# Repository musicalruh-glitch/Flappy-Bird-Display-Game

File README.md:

### **Flappy Bird Display Game**

I built a hand held game, the in game name being  "Flappy Bird Soul." The game is inspired by Undertale, (like all my other Half Life projects) and it was originally supposed to be a Flappy Bird game, hence the name but it's inspired by the attack patterns in game Undertale, sharing the same sprites and music. All credits for sprites, attack patterns, style, and music go to Toby Fox, this product is not for commercial use, it's for my own leisure, because if they won't make the merch just make it yourself! In any case, go play Undertale, it's awesome :D

!!DISCLAIMER FOR THE READ ME!! If you are an Undertale fan, you will have a field day. If you are not, you will be bombarded by references.

---

---

### **How it works:**

As I've mentioned, the game itself is heavily inspired by Undertale, every bit of it. I've had to make modifications since they're not the same thing -- obviously, but think of it as Undertale if it was a handheld Flappy-ish Bird game.

When you press the on/off button on the side, you're greeted with the title "Flappy Bird Soul" on the menu, along with a saved High Score and the prompt PRESS ANY TO START. To get started here, press any of the 4 directional buttons on the device to trigger the startup chime and launch straight into battle.

On the active gameplay screen you'll see the Undertale rectangular Battle Box, the HP: 20/20 counter in the top left, and your live SCR (score) counter in the top right. The entity you control? It's the classic soul from Undertale! It moves smoothly in 4 directions w/ no gravity (so not exactly flappy bird haha...). You'll have to dodge incoming obstacles like Papyrus's bone pillars or Toriel's fireballs, -- the two added attack patterns! Every obstacle you successfully dodge increases your score. If an obstacle hits your soul, it plays a damage sound effect and reduces your HP by 1. Once your HP is 0 you lose :(((

And the classic Game Over screen! You'll see big bold text reading "GAME OVER" accompanied by a descending chiptune shard-break sound effect, followed by a PRESS ANY TO RESET. Classic reset. When you reach this screen, as instructed press any button to save your high score and return to the main intro menu.

Usually for games like Flappy Bird there is no way to win the game (as far as I know); but that felt a bit half-baked for my taste, so if you last against the battle attacks for 10 whopping minutes,  you get the YOU WIN! display screen and the device tracks your total wins. Once you reach here, press any button to return to the menu for another run.

---

---

### **!!IMPORTANT FOR BILL OF MATERIALS!!
In Halflife I was told to add all the materials I would be using including anything I already own at $0, but Halflife requires everything added to be a minimum of $0.01 so everything listed to be $0.01 are things I already have!! Look at the BOM below for instructions for the custom PCB, the rest is basically a repeat of what's written in the Halflife BOM. FOR THE CUSTOM PCB PLEASE CHANGE SHIPPING TO GLOBAL STANDARD DIRECT LINE AND CHANGE THE SURFACE FINISH FROM Hasl (with lead) TO LeadFree HASL.**

---

### **Flappy Bird Display Game Project Bill of Materials (BOM)**

| Part / Description | Qty | Unit Price | Total Price | Vendor | Link |
| --- | --- | --- | --- | --- | --- |
| **Custom PCB** (Fabricated circuit board) | 1 | $5.20 | $5.20 | JLCPCB | https://cart.jlcpcb.com/quote?stencilLayer=2&stencilWidth=100&stencilLength=100&stencilCounts=5&plateType=1&spm=Jlcpcb.Homepage.1010
| **Seed Studio XIAO ESP32-S3** (Microcontroller) | 1 | $1.51 | $1.51 | AliExpress | https://www.aliexpress.us/item/3256813209030802.html?src=google&src=google&albch=shopping&acnt=708-803-3821&isdl=y&slnk=&plac=&mtctp=&albbt=Google_7_shopping&aff_platform=google&aff_short_key=UneMJZVf&gclsrc=aw.ds&albagn=888888&ds_e_adid=&ds_e_matchtype=&ds_e_device=c&ds_e_network=x&ds_e_product_group_id=&ds_e_product_id=en3256813209030802&ds_e_product_merchant_id=5851713403&ds_e_product_country=US&ds_e_product_language=en&ds_e_product_channel=online&ds_e_product_store_id=&ds_url_v=2&albcp=19558607238&albag=&isSmbAutoCall=false&needSmbHouyi=false&gad_source=1&gad_campaignid=19566915268&gbraid=0AAAAAD6I-hEBTz-5jNlmDqvFRvfd-Af1r&gclid=CjwKCAjwgJHXBhBGEiwAHohJq0jmxRYXkAyNDjMiczX3DgCREABbyFcu1fEiNRO9FfYQuq9aGSnCexoC5ZEQAvD_BwE&gatewayAdapt=glo2usa
| **0.96 inch SPI OLED Display** (128x64 resolution) | 1 | $1.09 | $1.09 | AliExpress | https://www.aliexpress.us/item/3256810259894244.html?src=google&src=google&albch=shopping&acnt=708-803-3821&isdl=y&slnk=&plac=&mtctp=&albbt=Google_7_shopping&aff_platform=google&aff_short_key=UneMJZVf&gclsrc=aw.ds&albagn=888888&ds_e_adid=&ds_e_matchtype=&ds_e_device=c&ds_e_network=x&ds_e_product_group_id=&ds_e_product_id=en3256810259894244&ds_e_product_merchant_id=5851713403&ds_e_product_country=US&ds_e_product_language=en&ds_e_product_channel=online&ds_e_product_store_id=&ds_url_v=2&albcp=19558607238&albag=&isSmbAutoCall=false&needSmbHouyi=false&gad_source=1&gad_campaignid=19566915268&gbraid=0AAAAAD6I-hEBTz-5jNlmDqvFRvfd-Af1r&gclid=CjwKCAjwgJHXBhBGEiwAHohJqw27ODRaYlOE_lPz4eLpTx0uXy4irya2ANM2uJhlEW0BOKlUSSg7PhoCdeUQAvD_BwE&gatewayAdapt=glo2usa
| **Tactile Push Buttons** | 1 | $1.09 | $1.09 | AliExpress | https://www.aliexpress.us/item/3256808376799054.html?src=google&src=google&albch=shopping&acnt=708-803-3821&isdl=y&slnk=&plac=&mtctp=&albbt=Google_7_shopping&aff_platform=google&aff_short_key=UneMJZVf&gclsrc=aw.ds&albagn=888888&ds_e_adid=&ds_e_matchtype=&ds_e_device=c&ds_e_network=x&ds_e_product_group_id=&ds_e_product_id=en3256808376799054&ds_e_product_merchant_id=5851713403&ds_e_product_country=US&ds_e_product_language=en&ds_e_product_channel=online&ds_e_product_store_id=&ds_url_v=2&albcp=19558607238&albag=&isSmbAutoCall=false&needSmbHouyi=false&gad_source=4&gad_campaignid=19566915268&gbraid=0AAAAAD6I-hGDbaypQSEg9FIsHYtTg3l-U&gclid=CjwKCAjwgJHXBhBGEiwAHohJq2HiYEh7Nx0f8b8VAlV9QLfA9kqLMiwbQNcA2PXyUyvbKBT3iwDi2RoCYD0QAvD_BwE&gatewayAdapt=glo2usa
| **Piezo Buzzer** | 1 | $1.09 | $1.09 | AliExpress | https://www.aliexpress.us/item/3256806026983317.html?src=google&src=google&albch=shopping&acnt=708-803-3821&isdl=y&slnk=&plac=&mtctp=&albbt=Google_7_shopping&aff_platform=google&aff_short_key=UneMJZVf&gclsrc=aw.ds&albagn=888888&ds_e_adid=&ds_e_matchtype=&ds_e_device=c&ds_e_network=x&ds_e_product_group_id=&ds_e_product_id=en3256806026983317&ds_e_product_merchant_id=5851713403&ds_e_product_country=US&ds_e_product_language=en&ds_e_product_channel=online&ds_e_product_store_id=&ds_url_v=2&albcp=19558607238&albag=&isSmbAutoCall=false&needSmbHouyi=false&gad_source=1&gad_campaignid=19566915268&gbraid=0AAAAAD6I-hEBTz-5jNlmDqvFRvfd-Af1r&gclid=CjwKCAjwgJHXBhBGEiwAHohJq_DGYuMpHG2ntfV_2_tf42pQ_JDr3ubO-9eQ19pHfD63iBxA8MtnLxoCD8EQAvD_BwE&gatewayAdapt=glo2usa

*Use gerber files to drag and drop in JLCPCB to order, and change shipping to Global Standard Direct Line
*Total Tax calculated is based off the fact that items that share the same source are put into a cart and then the shipping tax used for those items is combined to minimize cost
* **Total Tax & Shipping for the whole order:** $4.99

---

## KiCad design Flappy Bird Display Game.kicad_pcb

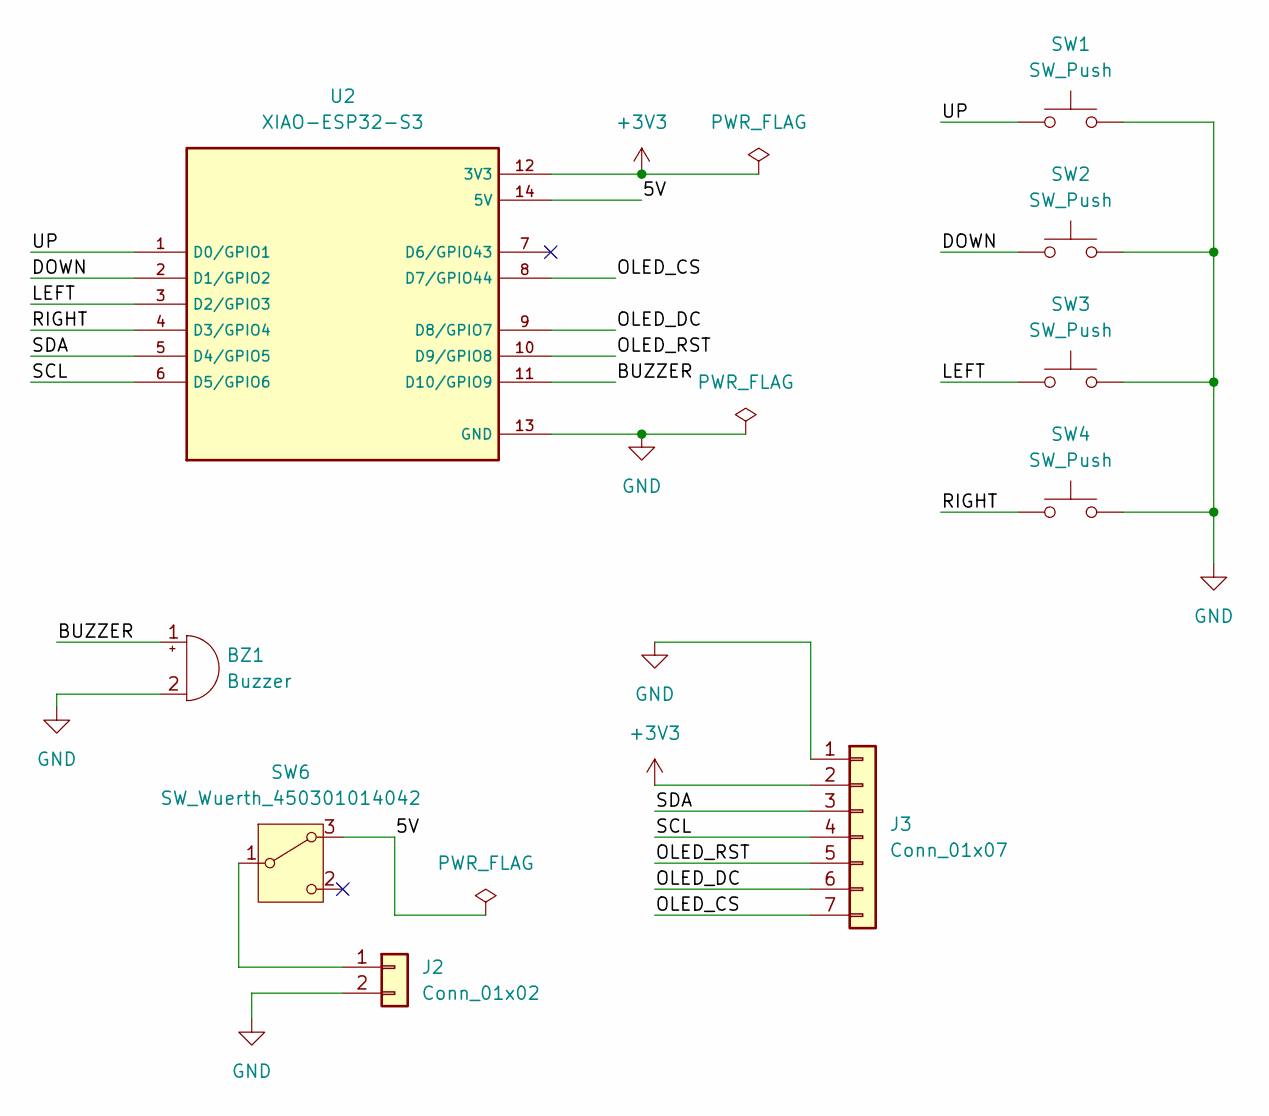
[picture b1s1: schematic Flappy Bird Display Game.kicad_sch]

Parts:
BZ1: Buzzer; Buzzer_12x9.5RM7.6
J2: Conn_01x02; PinHeader_1x02_P2.54mm_Vertical
J3: Conn_01x07; PinHeader_1x07_P2.54mm_Vertical
SW1, SW2, SW3, SW4: SW_Push; SW_PUSH_6mm_H7.3mm
SW6: SW_Wuerth_450301014042; SW_Slide-03_Wuerth-WS-SLTV_10x2.5x6.4_P2.54mm
U2: XIAO-ESP32-S3; XIAO ESP32-S3; PARTREV April 22nd, 2026

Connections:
+3V3: J3.2, U2.12 (3V3)
/5V: SW6.3 (A), U2.14 (5V)
/BUZZER: BZ1.1 (+), U2.11 (D10/GPIO9)
/DOWN: SW2.1, U2.2 (D1/GPIO2)
/LEFT: SW3.1, U2.3 (D2/GPIO3)
/OLED_CS: J3.7, U2.8 (D7/GPIO44)
/OLED_DC: J3.6, U2.9 (D8/GPIO7)
/OLED_RST: J3.5, U2.10 (D9/GPIO8)
/RIGHT: SW4.1, U2.4 (D3/GPIO4)
/SCL: J3.4, U2.6 (D5/GPIO6)
/SDA: J3.3, U2.5 (D4/GPIO5)
/UP: SW1.1, U2.1 (D0/GPIO1)
GND: BZ1.2 (-), J2.2, J3.1, SW1.2, SW2.2, SW3.2, SW4.2, U2.13 (GND)
unnamed: J2.1, SW6.1 (B)

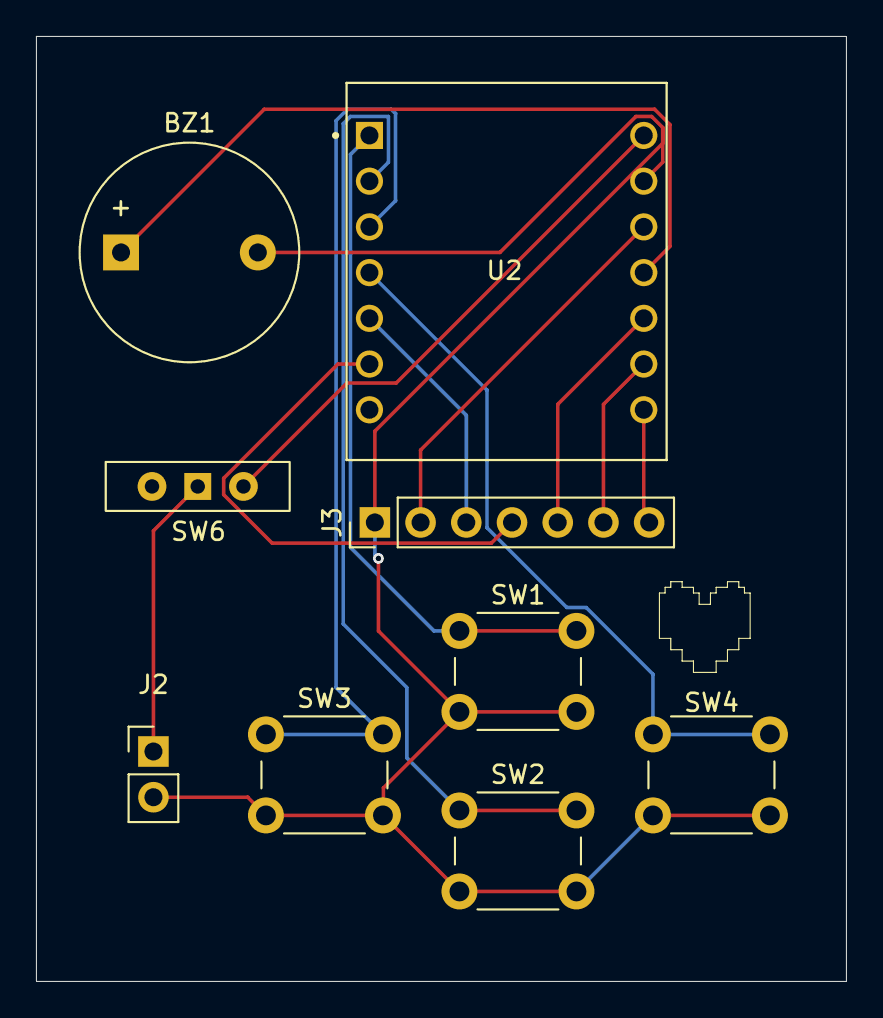
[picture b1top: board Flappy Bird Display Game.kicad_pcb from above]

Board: 2 copper layers, 45.0 x 52.5 mm, 9 parts (0 on the bottom side), 14 nets.

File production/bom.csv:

Designator,Footprint,Quantity,Value,LCSC Part #
BZ1,Buzzer_12x9.5RM7.6,1,Buzzer,
J2,PinHeader_1x02_P2.54mm_Vertical,1,Conn_01x02,
J3,PinHeader_1x07_P2.54mm_Vertical,1,Conn_01x07,
"SW1, SW2, SW3, SW4",SW_PUSH_6mm_H7.3mm,4,SW_Push,
SW6,SW_Slide-03_Wuerth-WS-SLTV_10x2.5x6.4_P2.54mm,1,SW_Wuerth_450301014042,
U2,XIAO ESP32-S3,1,XIAO-ESP32-S3,

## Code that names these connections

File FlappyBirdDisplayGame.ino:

#include <SPI.h>
#include <Wire.h>
#include <Adafruit_GFX.h>
#include <Adafruit_SSD1306.h>

//screen dimensions for the .96" OLED
#define SCREEN_WIDTH 128
#define SCREEN_HEIGHT 64

//hardware SPI ins for the 7-pin OLED display based on schematic
#define OLED_DC   9
#define OLED_CS   6
#define OLED_RST  8

//intialize the SSD1306 display using hardware SPI
Adafruit_SSD1306 display(SCREEN_WIDTH, SCREEN_HEIGHT, &SPI, OLED_DC, OLED_RST, OLED_CS);

//button pin definitions(connected to D0 through D3)
const int PIN_UP     = 0;
const int PIN_DOWN   = 1;
const int PIN_LEFT   = 2;
const int PIN_RIGHT  = 3;

//buzzer pin definition (connected to D10)
const int PIN_BUZZER = 10;

//helper function to play notes on the piezo buzzer
void playTone(int frequency, int duration) {
  tone(PIN_BUZZER, frequency, duration);
  delay(duration);
  noTone(PIN_BUZZER);
}

void setup() {
  // start serial monitor for debugging
  Serial.begin(115200);

  //configure button pins w/ internal pull-ups (so pressing them pulls the signal to LOW)
  pinMode(PIN_UP, INPUT_PULLUP);
  pinMode(PIN_DOWN, INPUT_PULLUP);
  pinMode(PIN_LEFT,INPUT_PULLUP);
  pinMode(PIN_RIGHT, INPUT_PULLUP);

  //configure buzzer pin as an output
  pinMode(PIN_BUZZER, OUTPUT);

  //intialize the SPI OLED display :DDD
  if(!display.begin(SSD1306_SWITCHCAPVCC)) {
    Serial.println(F("SSD1306 allocation failed"));
    for (;;); //stop execution if screen fails to intialize
  }

  //clear bufferand show a blank screen on startup
  display.clearDisplay();
  display.display();
}

//custom 8x8 undertale soul heart bitmap (PROGREM saves RAM)
const unsigned char PROGMEM soul_heart_bmp[] = {
  0b01100110,
  0b11111111,
  0b11111111,
  0b11111111,
  0b01111110,
  0b00111100,
  0b00011000,
  0b00000000
};

//game states: 0 = intro screen, 1 = gameplay, 2 = game over, 3 = win
int gameState = 0;
int highScore = 0;
int currentScore = 0;
int playerHp = 20;

//function to draw the undertale-themed intro screen
void drawIntroScreen() {
  display.clearDisplay();

  //title text
  display.setTextSize(1);
  display.setTextColor(SSD1306_WHITE);
  display.setCursor(12, 4);
  display.println(F("* FLAPPY BIRD SOUL *"));

  //high score display
  display.setCursor(20, 20);
  display.print(F("HIGH SCORE: "));
  display.println(highScore);

  //draw the soul heart logo on the menu
  display.drawBitmap(56, 34, soul_heart_bmp, 8, 8, SSD1306_WHITE);

  //press to start prompt
  display.setCursor(14, 52);
  display.print(F("PRESS ANY TO START"));

  display.display();
}

//define standard musical note frequencies for chiptune engine
#define NOTE_C4   262
#define NOTE_E4   330
#define NOTE_G4   396
#define NOTE_A4   440
#define NOTE_B4   494
#define NOTE_C5   523

//sound effect: heart hit/damage
void playHitSound() {
  tone(PIN_BUZZER, 150, 80);
  delay(90);
  tone(PIN_BUZZER, 100, 100);
  delay(110);
  noTone(PIN_BUZZER);
}

//sound effect: startup chime/flicker
void playStartupChime() {
  tone(PIN_BUZZER, NOTE_C4, 100); delay(120);
  tone(PIN_BUZZER, NOTE_E4, 100); delay(120);
  tone(PIN_BUZZER, NOTE_G4, 150); delay(170);
  noTone(PIN_BUZZER);
}

//sound effect: game over shard break
void playGameOverSound() {
  for(int i = 400; i > 100; i -= 50) {
    tone(PIN_BUZZER, i, 40);
    delay(45);
  }
  noTone(PIN_BUZZER);
}
//soul position and speed variables
int soulX = 60;
int soulY = 40;
int soulSpeed = 2;

//function to read buttons and move the soul in 4 directions
void updateSoulPosition() {
  if (digitalRead(PIN_UP) == LOW)       soulY -= soulSpeed;
  if (digitalRead(PIN_DOWN) == LOW)     soulY += soulSpeed;
  if (digitalRead(PIN_LEFT) == LOW)     soulX -= soulSpeed;
  if (digitalRead(PIN_RIGHT) == LOW)    soulX += soulSpeed;

  //restrict soul inside the battle box boundaries
  if (soulX < 16)  soulX = 16;
  if (soulX > 112)  soulX = 112;
  if (soulY < 24)  soulY = 24;
  if (soulY < 56)  soulY = 56;
}

//function to render the gameplay battle screen
void drawGameplayScreen() {
  display.clearDisplay();

  //draw the undertale battle box outline
  display.drawRect(12, 20, 104, 40, SSD1306_WHITE);

  //draw HP and score status text at the top
  display.setTextSize(1);
  display.setTextColor(SSD1306_WHITE);
  display.setCursor(12, 8);
  display.print(F("HP:"));
  display.print(playerHp);
  display.print(F("/20"));

  display.setCursor(76, 8);
  display.print(F("SCR:"));
  display.print(currentScore);

  //draw the soul heart at its current x and y position
  display.drawBitmap(soulX, soulY, soul_heart_bmp, 8, 8, SSD1306_WHITE);

  display.display();
}

//obstacle variables for Papyrus bones / Toriel's fireballs
int obstacleX = 110;
int obstacleY = 35;
int obstacleWidth = 6;
int obstacleHeight = 16;
int obstacleSpeed = 3;

//function to update obstacles and check collsions
void updateObstacles() {
  obstacleX -= obstacleSpeed;

  //if obstacle goes off screen, reset it to the right and increase score
  if (obstacleX <14) {
    obstacleX = 110;
    //randomize y pos within battle box
    obstacleY = 24 + (rand() % 25);
    currentScore++;
  }

  //bouding box collision detection between Soul (8x8) and obstacle
  if (soulX + 8 > obstacleX && soulX < obstacleX + obstacleWidth &&
      soulY + 8 > obstacleY && soulY < obstacleY + obstacleHeight) {

  //hit detected -- play buzzer sound and subtract HP
  playHitSound();
  playerHp -= 1;
  obstacleX = 110; //reset obstacle pos to prevent multi-hits

  //check if player runs out of health
  if (playerHp <= 0) {
    gameState = 2; // transition to game over state
    playGameOverSound();
      }
   }
}

//function to draw obstacles on screen
void drawObstacles() {
  display.fillRect(obstacleX, obstacleY, obstacleWidth, obstacleHeight, SSD1306_WHITE);
}

unsigned long gameStartTime = 0;
int totalWins = 0;//tracks total wins for the menu

void loop() {
  //state 0: intro menu screen
  if (gameState == 0) {
    drawIntroScreen();

    //press any button to start game hehe
    if (digitalRead(PIN_UP) == LOW || digitalRead(PIN_DOWN) == LOW ||
        digitalRead(PIN_LEFT) == LOW || digitalRead(PIN_RIGHT) == LOW) {
      playStartupChime();
      playerHp = 20;
      currentScore = 0;
      soulX = 60;
      soulY = 40;
      gameStartTime = millis(); //start the 10 minute clock
      gameState = 1;            //switch to gameplay
      delay(300);               //debounce delay
    }
}
//state 1: active gameplay loop
else if (gameState == 1) {
  updateSoulPosition();
  updateObstacles();
  drawGameplayScreen();

  //check for 10 min win condition (10 mins = 600,000 milliseconds)
  if (millis () - gameStartTime >= 600000) {
    gameState = 3; //Switch to Win screen
    totalWins++;
    if (currentScore > highScore) highScore = currentScore;
  }

  delay(30); //frame pacing for smooth animation (~30 FPS)
}
//state 2: game over screen
else if (gameState == 2) {
  display.clearDisplay();
  display.setTextSize(2);
  display.setTextColor(SSD1306_WHITE);
  display.setCursor(14, 15);
  display.print(F("GAME OVER"));
  display.setTextSize(1);
  display.setCursor(20, 45);
  display.print(F("PRESS ANY TO RESET"));
  display.display();

  //press any button to return to menu wheeeee
  if (digitalRead(PIN_UP) == LOW || digitalRead(PIN_DOWN) == LOW ||
      digitalRead(PIN_LEFT) == LOW || digitalRead(PIN_RIGHT) == LOW) {
    if (currentScore > highScore) highScore = currentScore;
    gameState = 0;
    delay(300);
  }
}
//state 3: win screen (10 min completion hoorayyyy)
else if (gameState == 3) {
  display.clearDisplay();
  display.setTextSize(2);
  display.setTextColor(SSD1306_WHITE);
  display.setCursor(24, 15);
  display.print(F("WINS:"));
  display.print(totalWins);
  display.display();

  //press any button to return to menu
  if (digitalRead(PIN_UP) == LOW || digitalRead(PIN_DOWN) == LOW ||
      digitalRead(PIN_LEFT) == LOW || digitalRead(PIN_RIGHT) ==LOW) {
    gameState = 0;
    delay(300);
    }
  }
}
